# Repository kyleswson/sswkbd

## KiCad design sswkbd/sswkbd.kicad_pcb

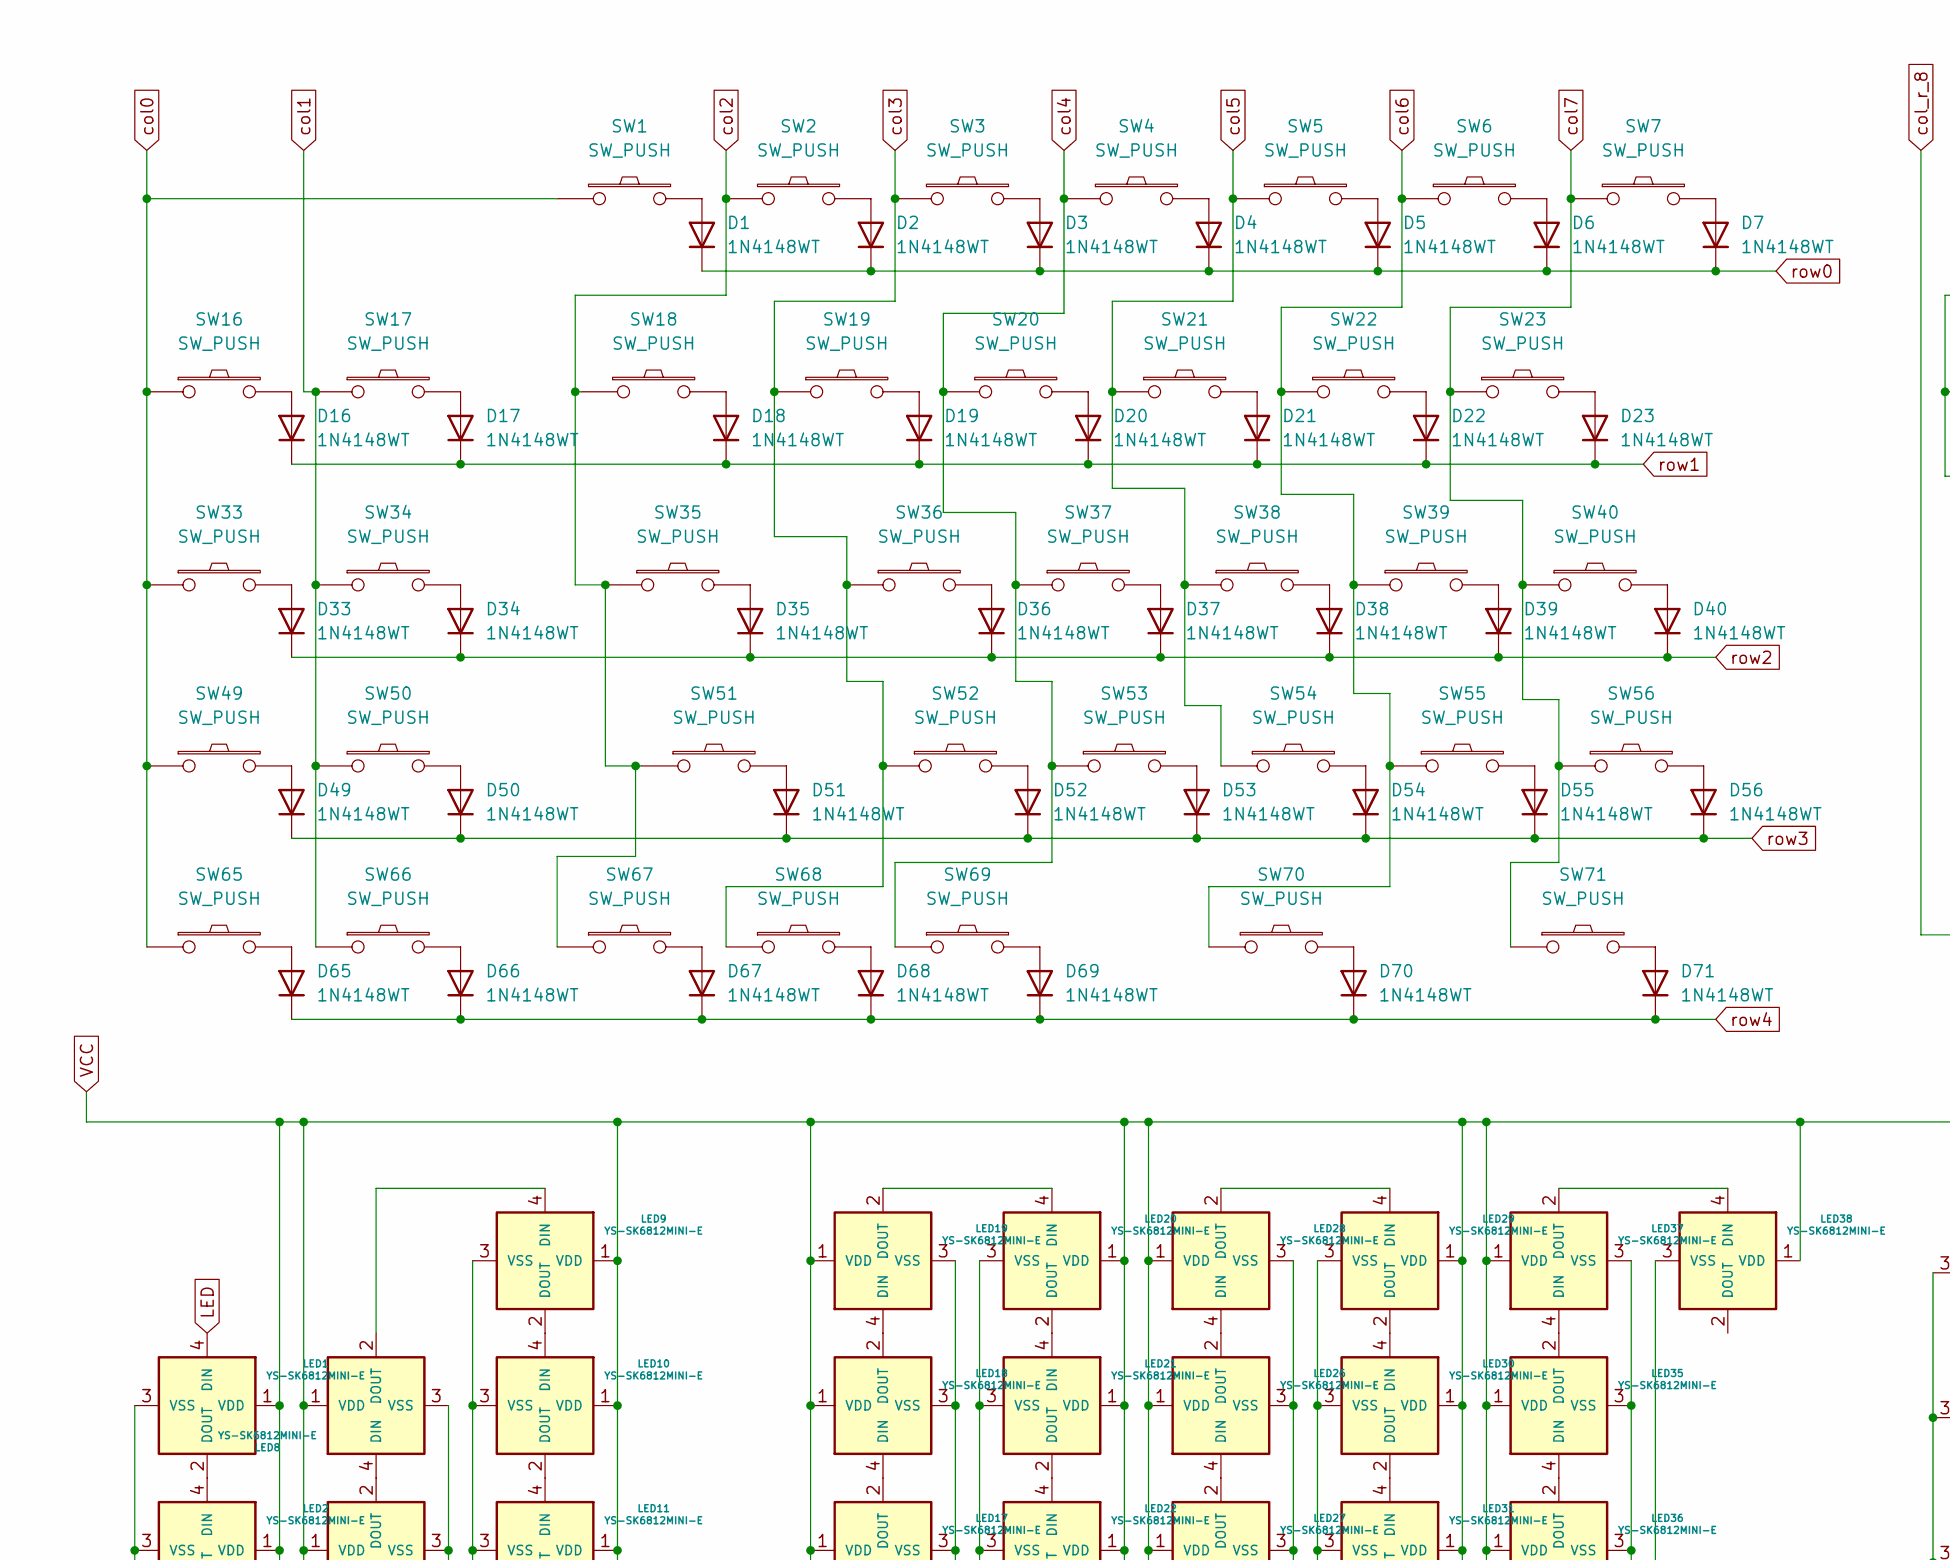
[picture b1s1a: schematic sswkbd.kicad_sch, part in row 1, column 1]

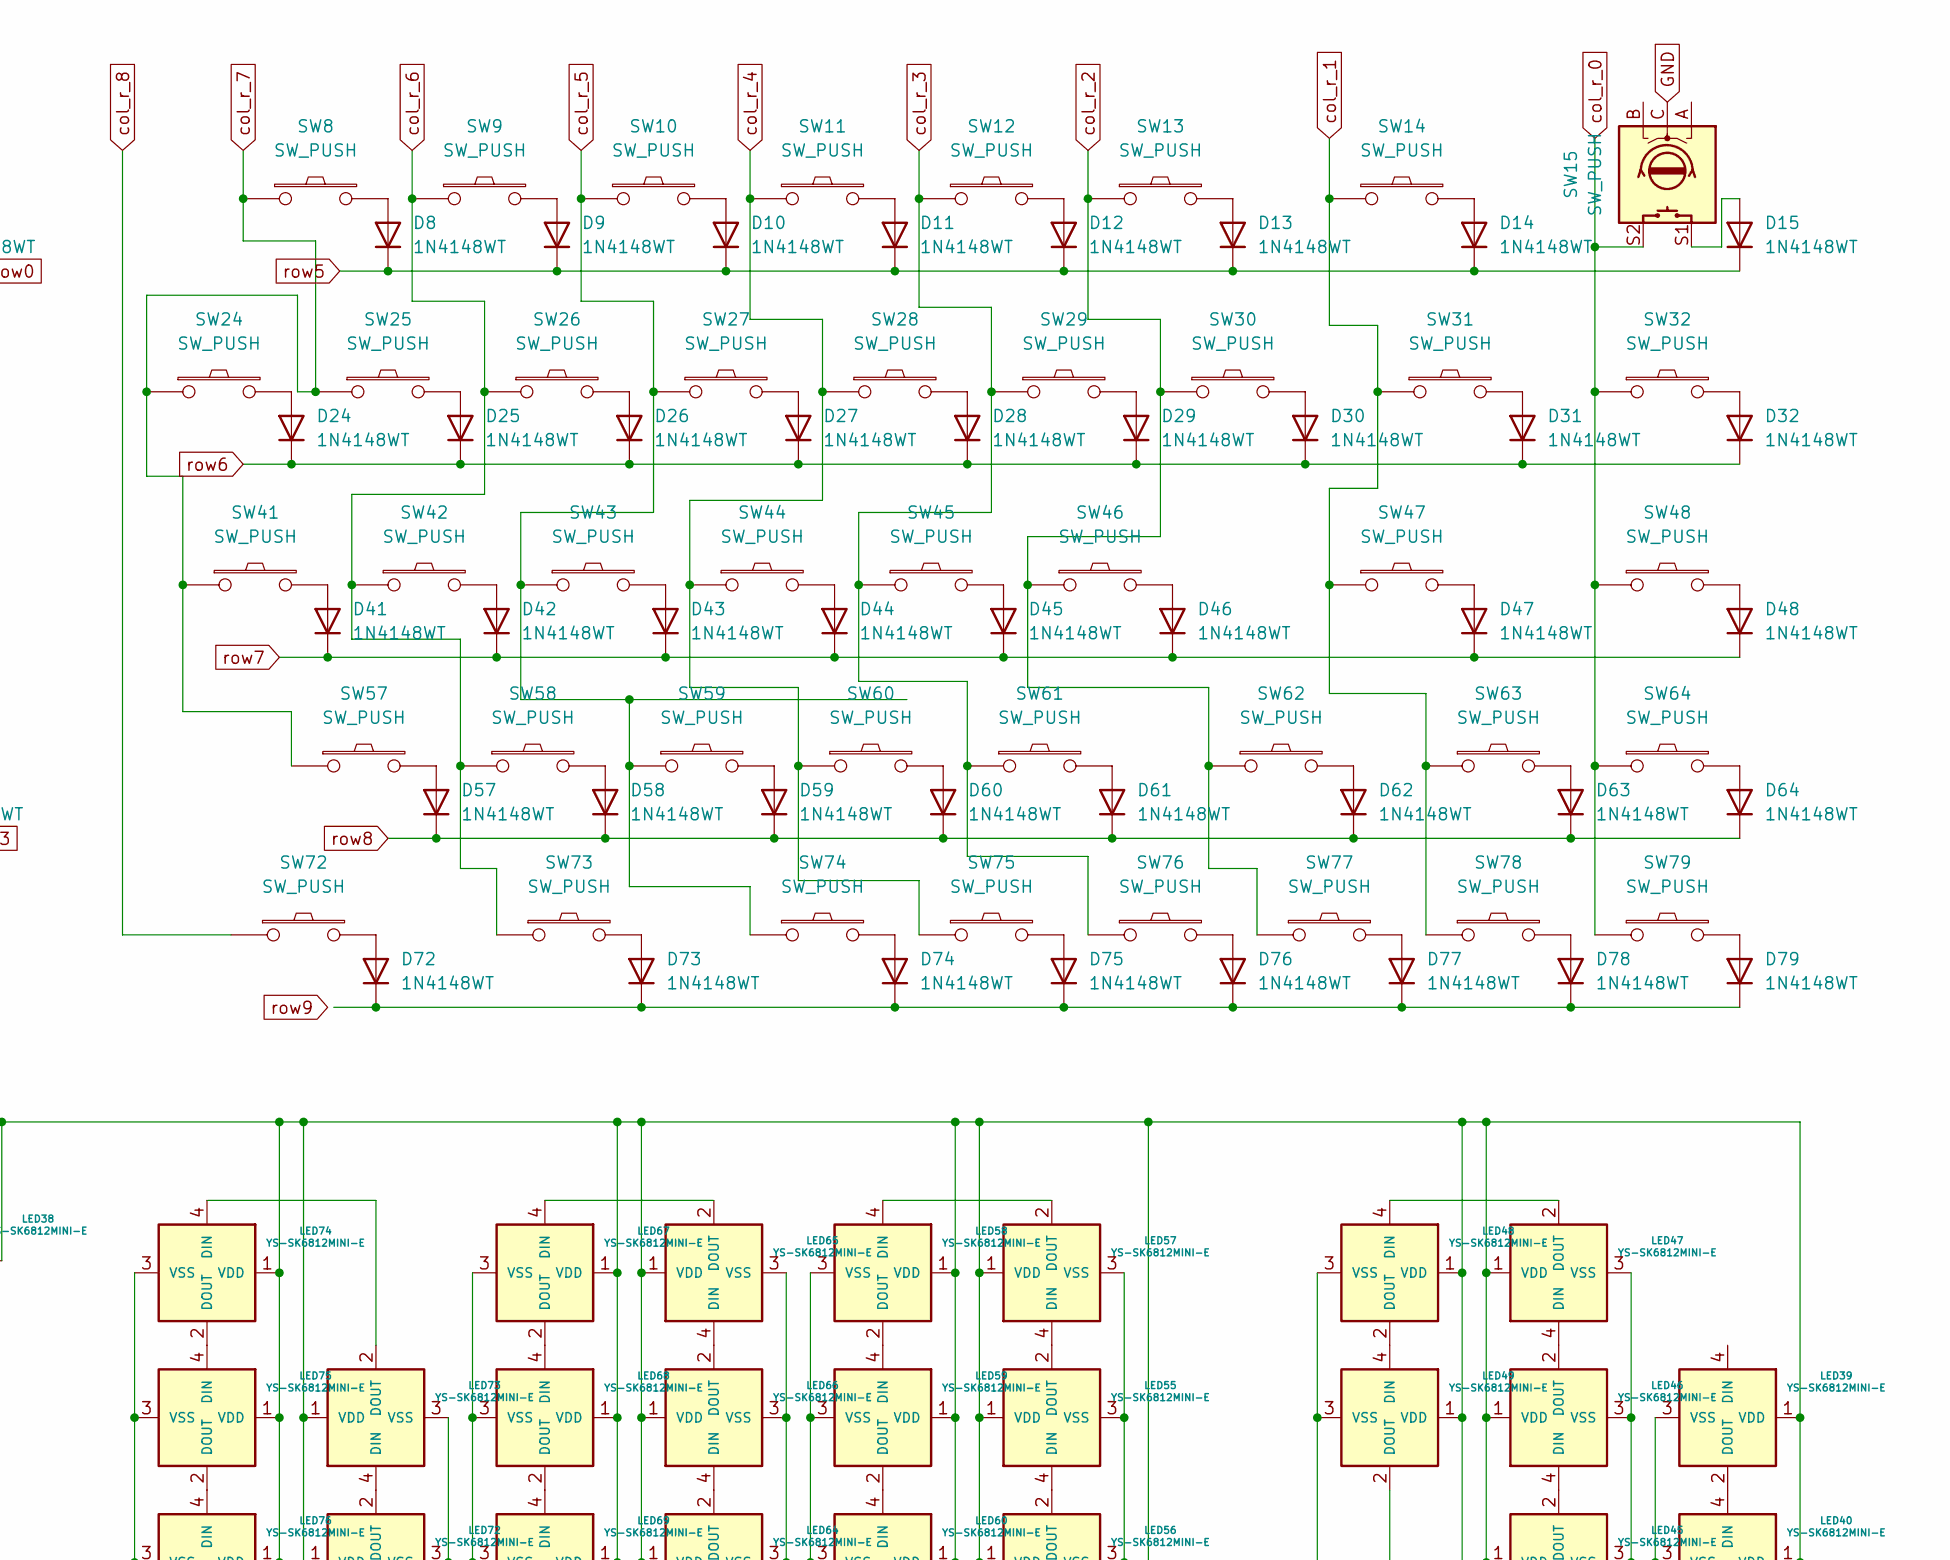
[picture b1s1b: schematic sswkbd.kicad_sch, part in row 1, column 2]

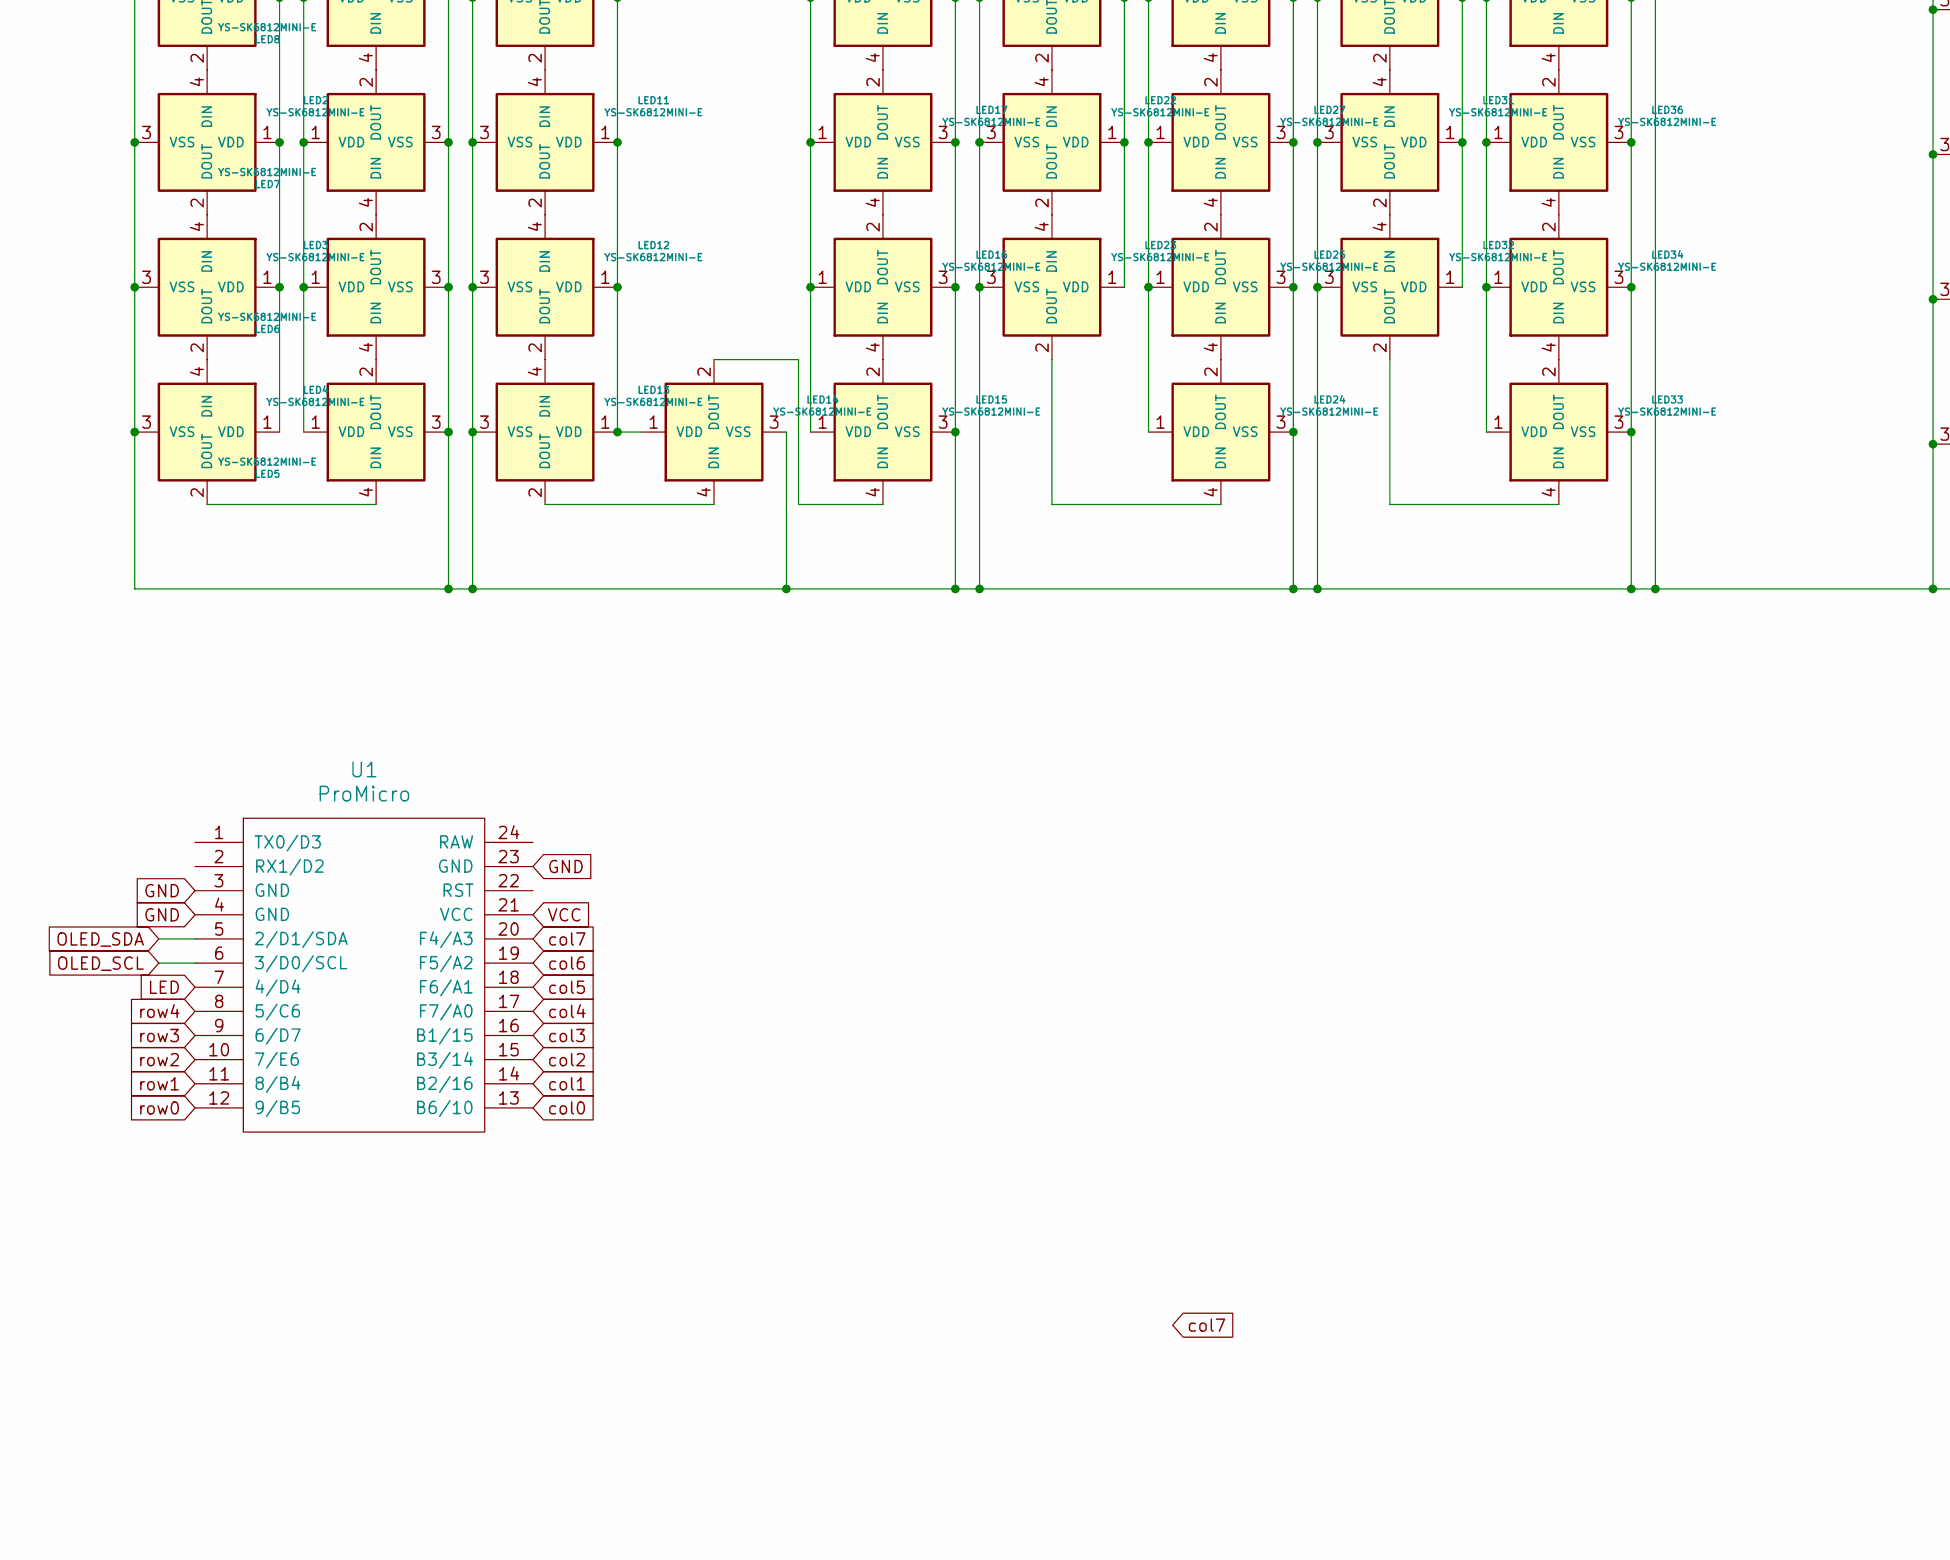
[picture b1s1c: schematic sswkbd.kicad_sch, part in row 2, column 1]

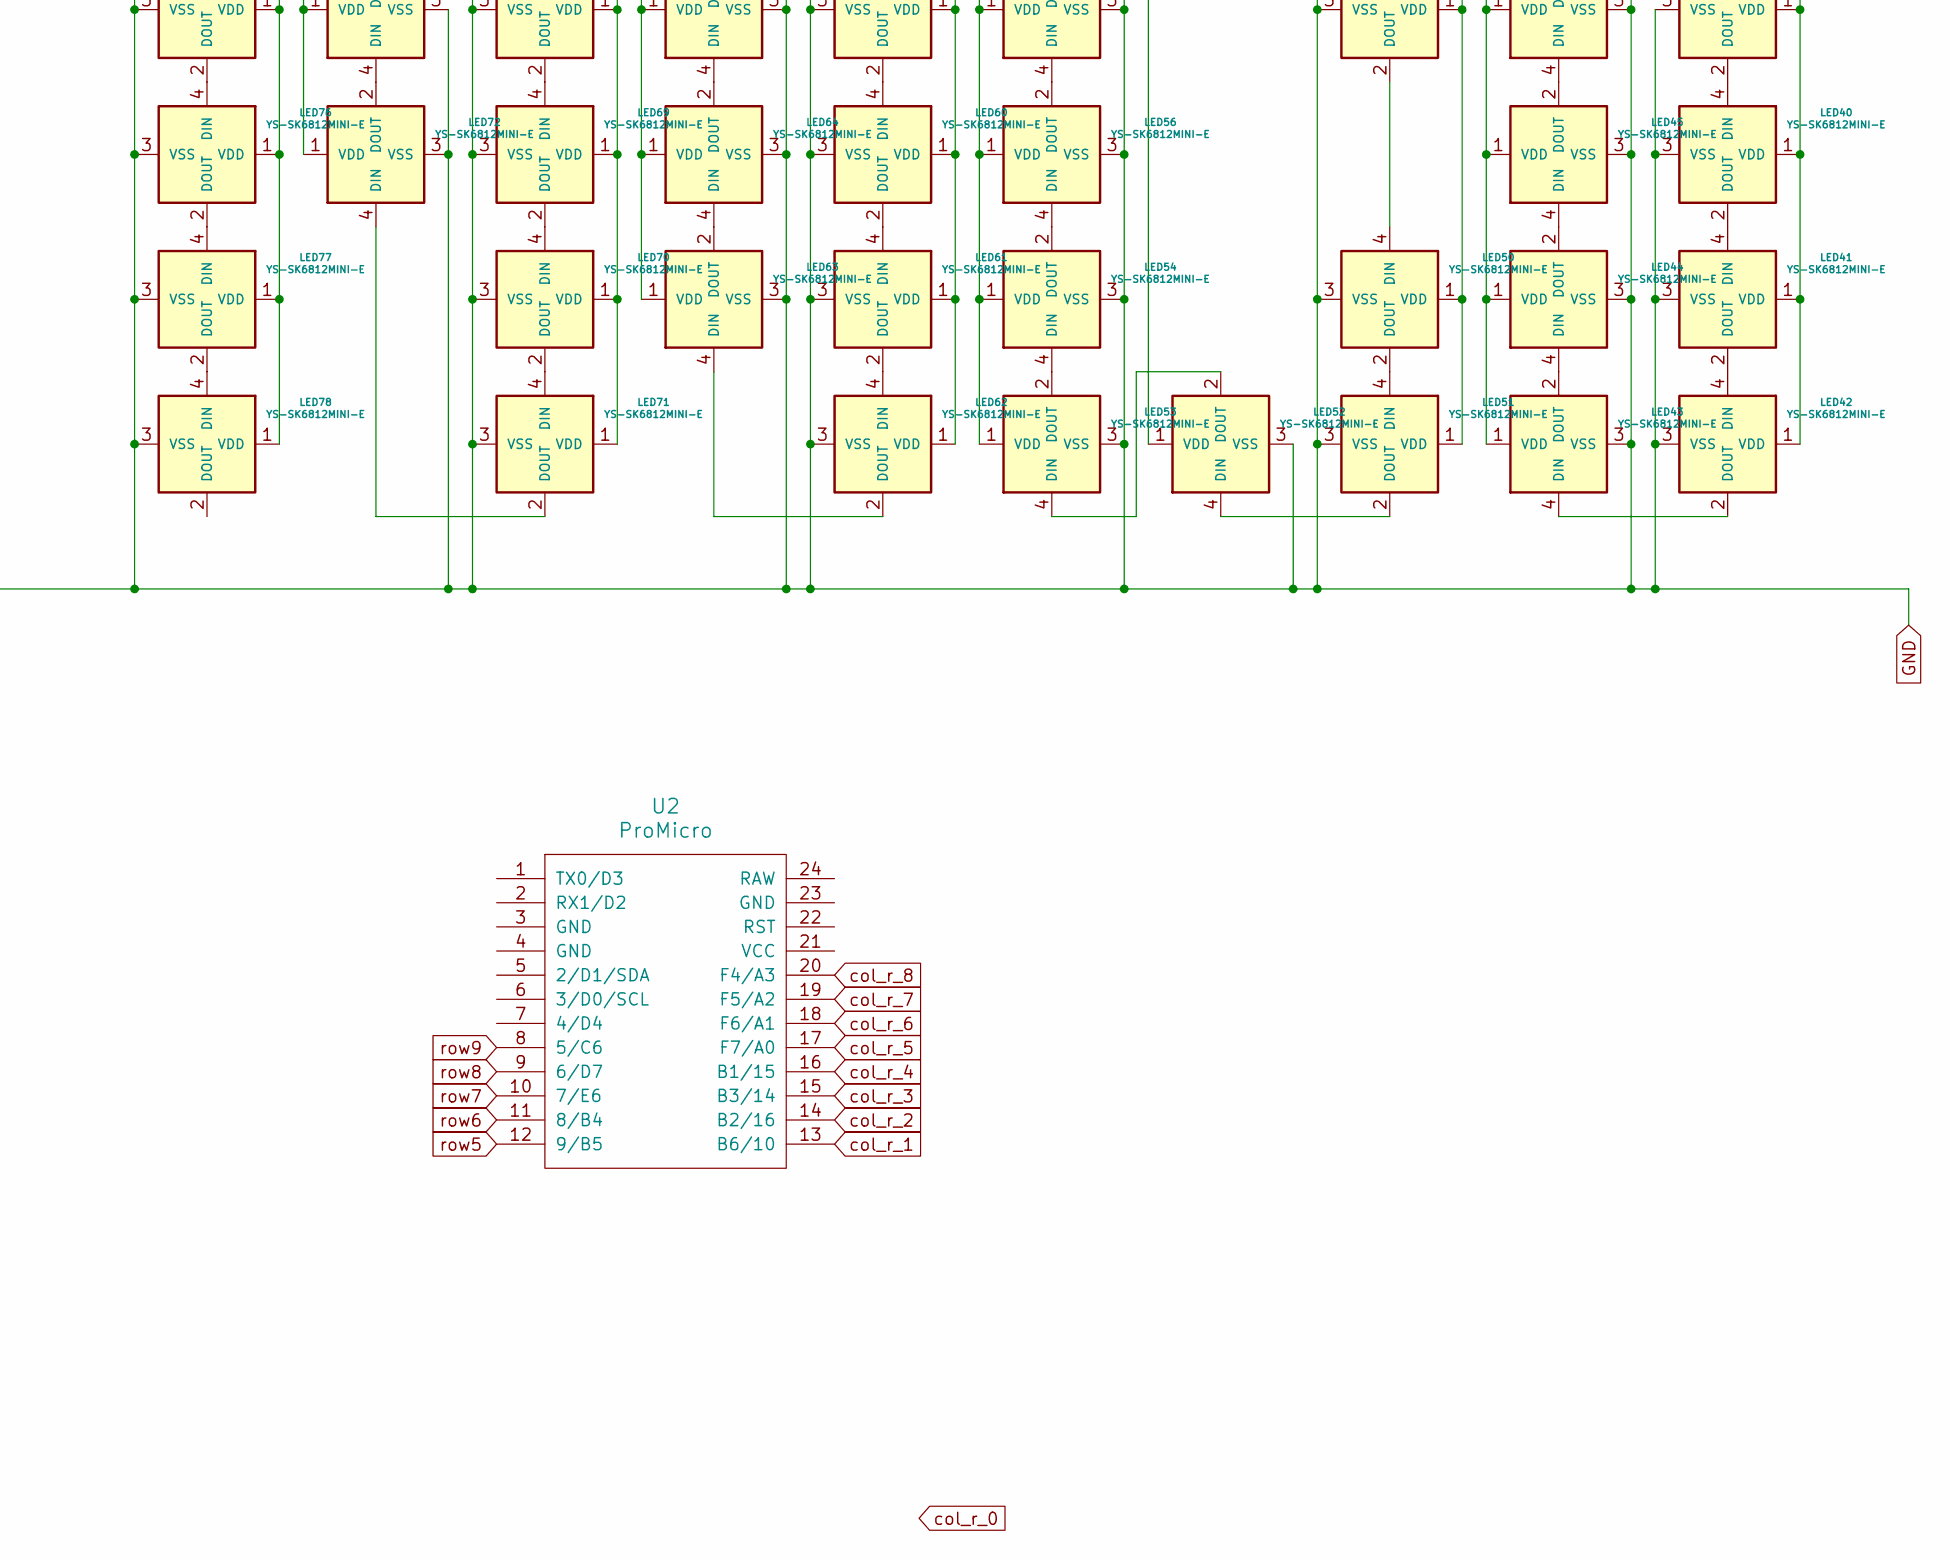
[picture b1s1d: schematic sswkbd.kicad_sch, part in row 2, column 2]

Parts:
D1, D2, D3, D4, D5, D6, D7, D8, D9, D10, D11, D12, D13, D14, D15, D16, D17, D18, D19, D20, D21, D22, D23, D24, D25, D26, D27, D28, D29, D30, D31, D32, D33, D34, D35, D36, D37, D38, D39, D40, D41, D42, D43, D44, D45, D46, D47, D48, D49, D50, D51, D52, D53, D54, D55, D56, D57, D58, D59, D60, D61, D62, D63, D64, D65, D66, D67, D68, D69, D70, D71, D72, D73, D74, D75, D76, D77, D78, D79: 1N4148WT; D3_TH_SMD
LED1, LED2, LED3, LED4, LED5, LED6, LED7, LED8, LED9, LED10, LED11, LED12, LED13, LED14, LED15, LED16, LED17, LED18, LED19, LED20, LED21, LED22, LED23, LED24, LED25, LED26, LED27, LED28, LED29, LED30, LED31, LED32, LED33, LED34, LED35, LED36, LED37, LED38, LED39, LED40, LED41, LED42, LED43, LED44, LED45, LED46, LED47, LED48, LED49, LED50, LED51, LED52, LED53, LED54, LED55, LED56, LED57, LED58, LED59, LED60, LED61, LED62, LED63, LED64, LED65, LED66, LED67, LED68, LED69, LED70, LED71, LED72, LED73, LED74, LED75, LED76, LED77, LED78: YS-SK6812MINI-E; SK6812MINI-E
SW1, SW2, SW3, SW4, SW5, SW6, SW7, SW8, SW9, SW10, SW11, SW12, SW13, SW16, SW17, SW19, SW20, SW21, SW22, SW23, SW24, SW25, SW26, SW27, SW28, SW29, SW30, SW32, SW33, SW34, SW36, SW37, SW38, SW39, SW40, SW41, SW42, SW43, SW44, SW45, SW46, SW48, SW49, SW50, SW52, SW53, SW54, SW55, SW56, SW57, SW58, SW59, SW60, SW61, SW63, SW64, SW65, SW66, SW67, SW68, SW69, SW71, SW72, SW74, SW75, SW76, SW77, SW78, SW79: SW_PUSH; MXOnly-1U-Hotswap
SW14: SW_PUSH; MXOnly-2U-Hotswap
SW15: SW_PUSH; keyswitch_cherrymx_hotswap_1u_rotary_encoder_ec12
SW18, SW31: SW_PUSH; MXOnly-1.5U-Hotswap
SW35, SW62: SW_PUSH; MXOnly-1.75U-Hotswap
SW47, SW51: SW_PUSH; MXOnly-2.25U-Hotswap
SW70: SW_PUSH; MXOnly-2.75U-Hotswap-ReversedStabilizers
SW73: SW_PUSH; MXOnly-2U-Hotswap-ReversedStabilizers
U1, U2: ProMicro

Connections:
GND: LED1.3 (VSS), LED2.3 (VSS), LED3.3 (VSS), LED4.3 (VSS), LED5.3 (VSS), LED6.3 (VSS), LED7.3 (VSS), LED8.3 (VSS), LED9.3 (VSS), LED10.3 (VSS), LED11.3 (VSS), LED12.3 (VSS), LED13.3 (VSS), LED14.3 (VSS), LED15.3 (VSS), LED16.3 (VSS), LED17.3 (VSS), LED18.3 (VSS), LED19.3 (VSS), LED20.3 (VSS), LED21.3 (VSS), LED22.3 (VSS), LED23.3 (VSS), LED24.3 (VSS), LED25.3 (VSS), LED26.3 (VSS), LED27.3 (VSS), LED28.3 (VSS), LED29.3 (VSS), LED30.3 (VSS), LED31.3 (VSS), LED32.3 (VSS), LED33.3 (VSS), LED34.3 (VSS), LED35.3 (VSS), LED36.3 (VSS), LED37.3 (VSS), LED38.3 (VSS), LED39.3 (VSS), LED40.3 (VSS), LED41.3 (VSS), LED42.3 (VSS), LED43.3 (VSS), LED44.3 (VSS), LED45.3 (VSS), LED46.3 (VSS), LED47.3 (VSS), LED48.3 (VSS), LED49.3 (VSS), LED50.3 (VSS), LED51.3 (VSS), LED52.3 (VSS), LED53.3 (VSS), LED54.3 (VSS), LED55.3 (VSS), LED56.3 (VSS), LED57.3 (VSS), LED58.3 (VSS), LED59.3 (VSS), LED60.3 (VSS), LED61.3 (VSS), LED62.3 (VSS), LED63.3 (VSS), LED64.3 (VSS), LED65.3 (VSS), LED66.3 (VSS), LED67.3 (VSS), LED68.3 (VSS), LED69.3 (VSS), LED70.3 (VSS), LED71.3 (VSS), LED72.3 (VSS), LED73.3 (VSS), LED74.3 (VSS), LED75.3 (VSS), LED76.3 (VSS), LED77.3 (VSS), LED78.3 (VSS), SW15.C, U1.3 (GND), U1.4 (GND), U1.23 (GND)
LED: LED1.4 (DIN), U1.7 (4/D4)
unnamed: D1.2 (A), SW1.2
unnamed: D2.2 (A), SW2.2
unnamed: D3.2 (A), SW3.2
unnamed: D4.2 (A), SW4.2
unnamed: D5.2 (A), SW5.2
unnamed: D6.2 (A), SW6.2
unnamed: D7.2 (A), SW7.2
unnamed: D8.2 (A), SW8.2
unnamed: D9.2 (A), SW9.2
unnamed: D10.2 (A), SW10.2
unnamed: D11.2 (A), SW11.2
unnamed: D12.2 (A), SW12.2
unnamed: D13.2 (A), SW13.2
unnamed: D14.2 (A), SW14.2
unnamed: D15.2 (A), SW15.S1
unnamed: D16.2 (A), SW16.2
unnamed: D17.2 (A), SW17.2
unnamed: D18.2 (A), SW18.2
unnamed: D19.2 (A), SW19.2
unnamed: D20.2 (A), SW20.2
unnamed: D21.2 (A), SW21.2
unnamed: D22.2 (A), SW22.2
unnamed: D23.2 (A), SW23.2
unnamed: D24.2 (A), SW24.2
unnamed: D25.2 (A), SW25.2
unnamed: D26.2 (A), SW26.2
unnamed: D27.2 (A), SW27.2
unnamed: D28.2 (A), SW28.2
unnamed: D29.2 (A), SW29.2
unnamed: D30.2 (A), SW30.2
unnamed: D31.2 (A), SW31.2
unnamed: D32.2 (A), SW32.2
unnamed: D33.2 (A), SW33.2
unnamed: D34.2 (A), SW34.2
unnamed: D35.2 (A), SW35.2
unnamed: D36.2 (A), SW36.2
unnamed: D37.2 (A), SW37.2
unnamed: D38.2 (A), SW38.2
unnamed: D39.2 (A), SW39.2
unnamed: D40.2 (A), SW40.2
unnamed: D41.2 (A), SW41.2
unnamed: D42.2 (A), SW42.2
unnamed: D43.2 (A), SW43.2
unnamed: D44.2 (A), SW44.2
unnamed: D45.2 (A), SW45.2
unnamed: D46.2 (A), SW46.2
unnamed: D47.2 (A), SW47.2
unnamed: D48.2 (A), SW48.2
unnamed: D49.2 (A), SW49.2
unnamed: D50.2 (A), SW50.2
unnamed: D51.2 (A), SW51.2
unnamed: D52.2 (A), SW52.2
unnamed: D53.2 (A), SW53.2
unnamed: D54.2 (A), SW54.2
unnamed: D55.2 (A), SW55.2
unnamed: D56.2 (A), SW56.2
unnamed: D57.2 (A), SW57.2
unnamed: D58.2 (A), SW58.2
unnamed: D59.2 (A), SW59.2
unnamed: D60.2 (A), SW60.2
unnamed: D61.2 (A), SW61.2
unnamed: D62.2 (A), SW62.2
unnamed: D63.2 (A), SW63.2
unnamed: D64.2 (A), SW64.2
unnamed: D65.2 (A), SW65.2
unnamed: D66.2 (A), SW66.2
unnamed: D67.2 (A), SW67.2
unnamed: D68.2 (A), SW68.2
unnamed: D69.2 (A), SW69.2
unnamed: D70.2 (A), SW70.2
unnamed: D71.2 (A), SW71.2
unnamed: D72.2 (A), SW72.2
unnamed: D72.1 (K), D73.1 (K), D74.1 (K), D75.1 (K), D76.1 (K), D77.1 (K), D78.1 (K), D79.1 (K)
unnamed: D73.2 (A), SW73.2
unnamed: D74.2 (A), SW74.2
unnamed: D75.2 (A), SW75.2
unnamed: D76.2 (A), SW76.2
unnamed: D77.2 (A), SW77.2
unnamed: D78.2 (A), SW78.2
unnamed: D79.2 (A), SW79.2
unnamed: LED1.2 (DOUT), LED2.4 (DIN)
unnamed: LED2.2 (DOUT), LED3.4 (DIN)
unnamed: LED3.2 (DOUT), LED4.4 (DIN)
unnamed: LED4.2 (DOUT), LED5.4 (DIN)
unnamed: LED5.2 (DOUT), LED6.4 (DIN)
unnamed: LED6.2 (DOUT), LED7.4 (DIN)
unnamed: LED7.2 (DOUT), LED8.4 (DIN)
unnamed: LED8.2 (DOUT), LED9.4 (DIN)
unnamed: LED9.2 (DOUT), LED10.4 (DIN)
unnamed: LED10.2 (DOUT), LED11.4 (DIN)
unnamed: LED11.2 (DOUT), LED12.4 (DIN)
unnamed: LED12.2 (DOUT), LED13.4 (DIN)
unnamed: LED13.2 (DOUT), LED14.4 (DIN)
unnamed: LED14.2 (DOUT), LED15.4 (DIN)
unnamed: LED15.2 (DOUT), LED16.4 (DIN)
unnamed: LED16.2 (DOUT), LED17.4 (DIN)
unnamed: LED17.2 (DOUT), LED18.4 (DIN)
unnamed: LED18.2 (DOUT), LED19.4 (DIN)
unnamed: LED19.2 (DOUT), LED20.4 (DIN)
unnamed: LED20.2 (DOUT), LED21.4 (DIN)
unnamed: LED21.2 (DOUT), LED22.4 (DIN)
unnamed: LED22.2 (DOUT), LED23.4 (DIN)
unnamed: LED23.2 (DOUT), LED24.4 (DIN)
unnamed: LED24.2 (DOUT), LED25.4 (DIN)
unnamed: LED25.2 (DOUT), LED27.4 (DIN)
unnamed: LED26.4 (DIN), LED27.2 (DOUT)
unnamed: LED26.2 (DOUT), LED28.4 (DIN)
unnamed: LED28.2 (DOUT), LED29.4 (DIN)
unnamed: LED29.2 (DOUT), LED30.4 (DIN)
unnamed: LED30.2 (DOUT), LED31.4 (DIN)
unnamed: LED31.2 (DOUT), LED32.4 (DIN)
unnamed: LED32.2 (DOUT), LED33.4 (DIN)
unnamed: LED33.2 (DOUT), LED34.4 (DIN)
unnamed: LED34.2 (DOUT), LED36.4 (DIN)
unnamed: LED35.4 (DIN), LED36.2 (DOUT)
unnamed: LED35.2 (DOUT), LED37.4 (DIN)
unnamed: LED37.2 (DOUT), LED38.4 (DIN)
unnamed: LED39.2 (DOUT), LED40.4 (DIN)
unnamed: LED40.2 (DOUT), LED41.4 (DIN)
unnamed: LED41.2 (DOUT), LED42.4 (DIN)
unnamed: LED42.2 (DOUT), LED43.4 (DIN)
unnamed: LED43.2 (DOUT), LED44.4 (DIN)
unnamed: LED44.2 (DOUT), LED45.4 (DIN)
unnamed: LED45.2 (DOUT), LED46.4 (DIN)
unnamed: LED46.2 (DOUT), LED47.4 (DIN)
unnamed: LED47.2 (DOUT), LED48.4 (DIN)
unnamed: LED48.2 (DOUT), LED49.4 (DIN)
unnamed: LED49.2 (DOUT), LED50.4 (DIN)
unnamed: LED50.2 (DOUT), LED51.4 (DIN)
unnamed: LED51.2 (DOUT), LED52.4 (DIN)
unnamed: LED52.2 (DOUT), LED53.4 (DIN)
unnamed: LED53.2 (DOUT), LED54.4 (DIN)
unnamed: LED54.2 (DOUT), LED56.4 (DIN)
unnamed: LED55.4 (DIN), LED56.2 (DOUT)
unnamed: LED55.2 (DOUT), LED57.4 (DIN)
unnamed: LED57.2 (DOUT), LED58.4 (DIN)
unnamed: LED58.2 (DOUT), LED59.4 (DIN)
unnamed: LED59.2 (DOUT), LED60.4 (DIN)
unnamed: LED60.2 (DOUT), LED61.4 (DIN)
unnamed: LED61.2 (DOUT), LED62.4 (DIN)
unnamed: LED62.2 (DOUT), LED63.4 (DIN)
unnamed: LED63.2 (DOUT), LED64.4 (DIN)
unnamed: LED64.2 (DOUT), LED66.4 (DIN)
unnamed: LED65.4 (DIN), LED66.2 (DOUT)
unnamed: LED65.2 (DOUT), LED67.4 (DIN)
unnamed: LED67.2 (DOUT), LED68.4 (DIN)
unnamed: LED68.2 (DOUT), LED69.4 (DIN)
unnamed: LED69.2 (DOUT), LED70.4 (DIN)
unnamed: LED70.2 (DOUT), LED71.4 (DIN)
unnamed: LED71.2 (DOUT), LED72.4 (DIN)
unnamed: LED72.2 (DOUT), LED73.4 (DIN)
unnamed: LED73.2 (DOUT), LED74.4 (DIN)
unnamed: LED74.2 (DOUT), LED75.4 (DIN)
unnamed: LED75.2 (DOUT), LED76.4 (DIN)
unnamed: LED76.2 (DOUT), LED77.4 (DIN)
unnamed: LED77.2 (DOUT), LED78.4 (DIN)
OLED_SCL: U1.6 (3/D0/SCL)
OLED_SDA: U1.5 (2/D1/SDA)
VCC: LED1.1 (VDD), LED2.1 (VDD), LED3.1 (VDD), LED4.1 (VDD), LED5.1 (VDD), LED6.1 (VDD), LED7.1 (VDD), LED8.1 (VDD), LED9.1 (VDD), LED10.1 (VDD), LED11.1 (VDD), LED12.1 (VDD), LED13.1 (VDD), LED14.1 (VDD), LED15.1 (VDD), LED16.1 (VDD), LED17.1 (VDD), LED18.1 (VDD), LED19.1 (VDD), LED20.1 (VDD), LED21.1 (VDD), LED22.1 (VDD), LED23.1 (VDD), LED24.1 (VDD), LED25.1 (VDD), LED26.1 (VDD), LED27.1 (VDD), LED28.1 (VDD), LED29.1 (VDD), LED30.1 (VDD), LED31.1 (VDD), LED32.1 (VDD), LED33.1 (VDD), LED34.1 (VDD), LED35.1 (VDD), LED36.1 (VDD), LED37.1 (VDD), LED38.1 (VDD), LED39.1 (VDD), LED40.1 (VDD), LED41.1 (VDD), LED42.1 (VDD), LED43.1 (VDD), LED44.1 (VDD), LED45.1 (VDD), LED46.1 (VDD), LED47.1 (VDD), LED48.1 (VDD), LED49.1 (VDD), LED50.1 (VDD), LED51.1 (VDD), LED52.1 (VDD), LED53.1 (VDD), LED54.1 (VDD), LED55.1 (VDD), LED56.1 (VDD), LED57.1 (VDD), LED58.1 (VDD), LED59.1 (VDD), LED60.1 (VDD), LED61.1 (VDD), LED62.1 (VDD), LED63.1 (VDD), LED64.1 (VDD), LED65.1 (VDD), LED66.1 (VDD), LED67.1 (VDD), LED68.1 (VDD), LED69.1 (VDD), LED70.1 (VDD), LED71.1 (VDD), LED72.1 (VDD), LED73.1 (VDD), LED74.1 (VDD), LED75.1 (VDD), LED76.1 (VDD), LED77.1 (VDD), LED78.1 (VDD), U1.21 (VCC)
col0: SW1.1, SW16.1, SW33.1, SW49.1, SW65.1, U1.13 (B6/10)
col1: SW17.1, SW34.1, SW50.1, SW66.1, U1.14 (B2/16)
col2: SW2.1, SW18.1, SW35.1, SW51.1, SW67.1, U1.15 (B3/14)
col3: SW3.1, SW19.1, SW36.1, SW52.1, SW68.1, U1.16 (B1/15)
col4: SW4.1, SW20.1, SW37.1, SW53.1, SW69.1, U1.17 (F7/A0)
col5: SW5.1, SW21.1, SW38.1, SW54.1, U1.18 (F6/A1)
col6: SW6.1, SW22.1, SW39.1, SW55.1, SW70.1, U1.19 (F5/A2)
col7: SW7.1, SW23.1, SW40.1, SW56.1, SW71.1, U1.20 (F4/A3)
col_r_0: SW15.S2, SW32.1, SW48.1, SW64.1, SW79.1
col_r_1: SW14.1, SW31.1, SW47.1, SW63.1, SW78.1, U2.13 (B6/10)
col_r_2: SW13.1, SW30.1, SW46.1, SW62.1, SW77.1, U2.14 (B2/16)
col_r_3: SW12.1, SW29.1, SW45.1, SW61.1, SW76.1, U2.15 (B3/14)
col_r_4: SW11.1, SW28.1, SW44.1, SW60.1, SW75.1, U2.16 (B1/15)
col_r_5: SW10.1, SW27.1, SW43.1, SW59.1, SW74.1, U2.17 (F7/A0)
col_r_6: SW9.1, SW26.1, SW42.1, SW58.1, SW73.1, U2.18 (F6/A1)
col_r_7: SW8.1, SW24.1, SW25.1, SW41.1, SW57.1, U2.19 (F5/A2)
col_r_8: SW72.1, U2.20 (F4/A3)
row0: D1.1 (K), D2.1 (K), D3.1 (K), D4.1 (K), D5.1 (K), D6.1 (K), D7.1 (K), U1.12 (9/B5)
row1: D16.1 (K), D17.1 (K), D18.1 (K), D19.1 (K), D20.1 (K), D21.1 (K), D22.1 (K), D23.1 (K), U1.11 (8/B4)
row2: D33.1 (K), D34.1 (K), D35.1 (K), D36.1 (K), D37.1 (K), D38.1 (K), D39.1 (K), D40.1 (K), U1.10 (7/E6)
row3: D49.1 (K), D50.1 (K), D51.1 (K), D52.1 (K), D53.1 (K), D54.1 (K), D55.1 (K), D56.1 (K), U1.9 (6/D7)
row4: D65.1 (K), D66.1 (K), D67.1 (K), D68.1 (K), D69.1 (K), D70.1 (K), D71.1 (K), U1.8 (5/C6)
row5: D8.1 (K), D9.1 (K), D10.1 (K), D11.1 (K), D12.1 (K), D13.1 (K), D14.1 (K), D15.1 (K), U2.12 (9/B5)
row6: D24.1 (K), D25.1 (K), D26.1 (K), D27.1 (K), D28.1 (K), D29.1 (K), D30.1 (K), D31.1 (K), D32.1 (K), U2.11 (8/B4)
row7: D41.1 (K), D42.1 (K), D43.1 (K), D44.1 (K), D45.1 (K), D46.1 (K), D47.1 (K), D48.1 (K), U2.10 (7/E6)
row8: D57.1 (K), D58.1 (K), D59.1 (K), D60.1 (K), D61.1 (K), D62.1 (K), D63.1 (K), D64.1 (K), U2.9 (6/D7)
row9: U2.8 (5/C6)

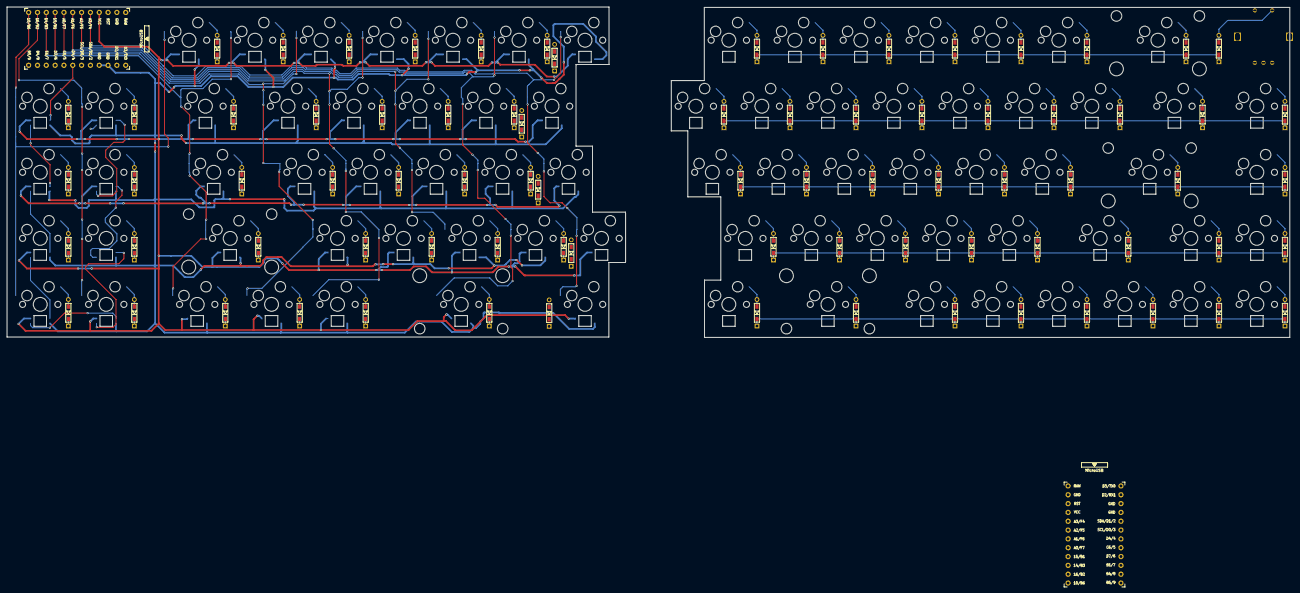
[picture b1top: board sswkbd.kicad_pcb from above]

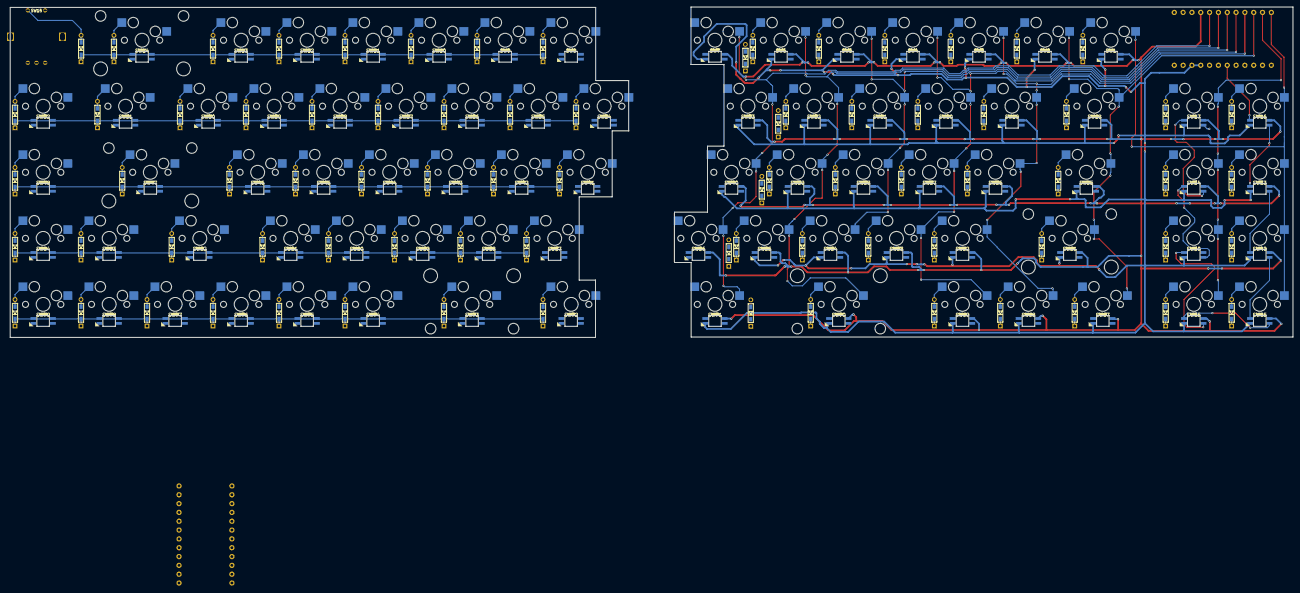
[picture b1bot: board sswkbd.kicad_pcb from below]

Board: 2 copper layers, 369.3 x 95.1 mm, 238 parts (80 on the bottom side), 185 nets.

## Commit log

2025-04-02 sswkbd_PCB
2025-04-03 PCB WIP
2025-04-09 wiring WIP
2025-04-09 usbport position
2025-04-11 PCB silkscreen
2025-04-15 Edge cut WIP
2025-04-16 Silkscreen
2025-04-17 Done!
2025-04-30 QMK fw
